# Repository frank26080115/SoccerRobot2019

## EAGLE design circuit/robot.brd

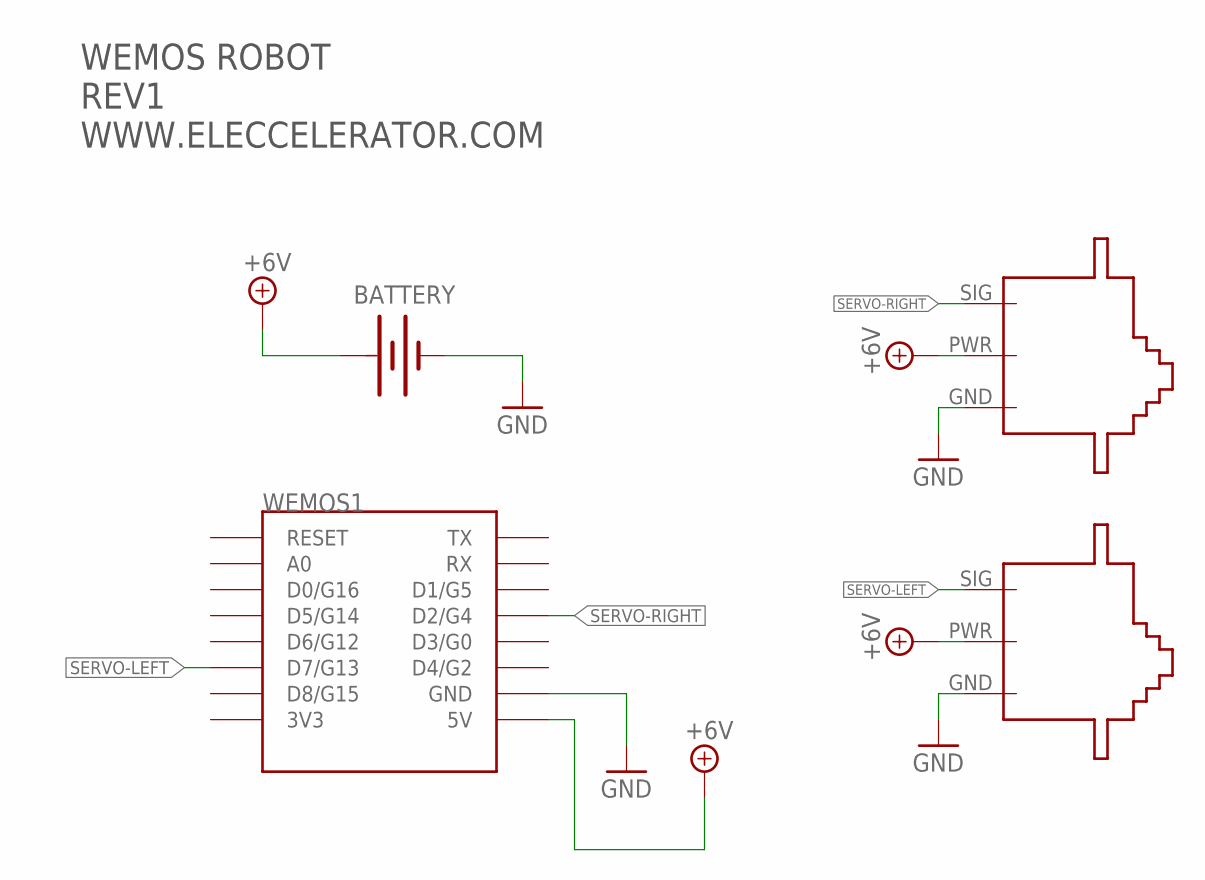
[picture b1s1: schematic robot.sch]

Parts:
BATTERY: BATTERY-WIRE-CONN; BATT-WIRE-CONN
M1: SERVO-FLIPPED
M2: SERVO-1; SERVO
U$1: HACKADAY-14MM; HACKADAY-1
U$9: TEXT-INFO-MINI
WEMOS1: WEMOS-D1-MINI

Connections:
+6V: BATTERY.POS (+), M1.PWR, M2.PWR, WEMOS1.5V
GND: BATTERY.NEG (-), M1.GND, M2.GND, WEMOS1.GND
SERVO-LEFT: M1.SIG, WEMOS1.D7 (D7/G13)
SERVO-RIGHT: M2.SIG, WEMOS1.D2 (D2/G4)

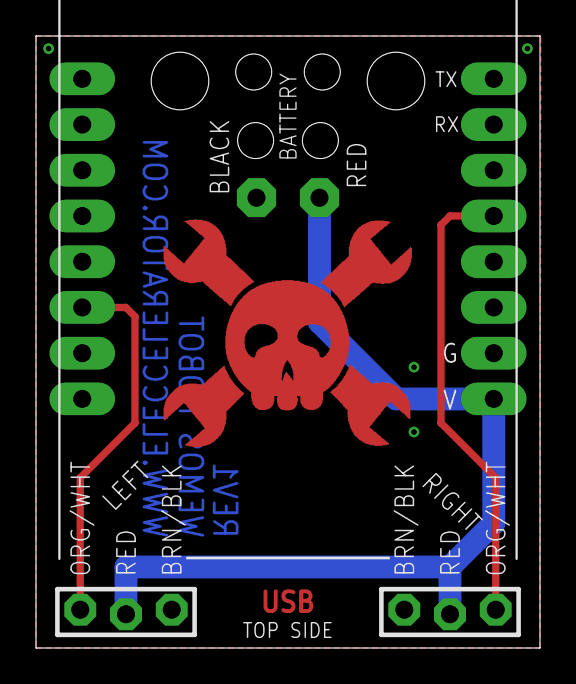
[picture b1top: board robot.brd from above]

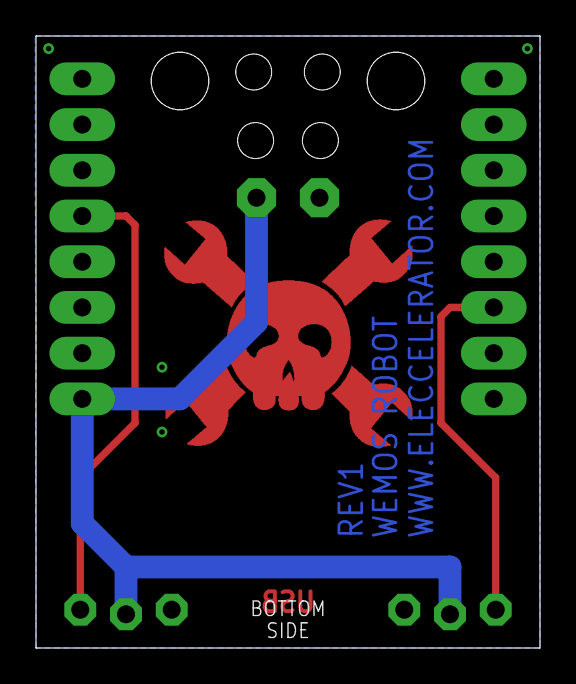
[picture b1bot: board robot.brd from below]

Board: 2 copper layers, 28.0 x 34.0 mm, 6 parts (2 on the bottom side), 4 nets.

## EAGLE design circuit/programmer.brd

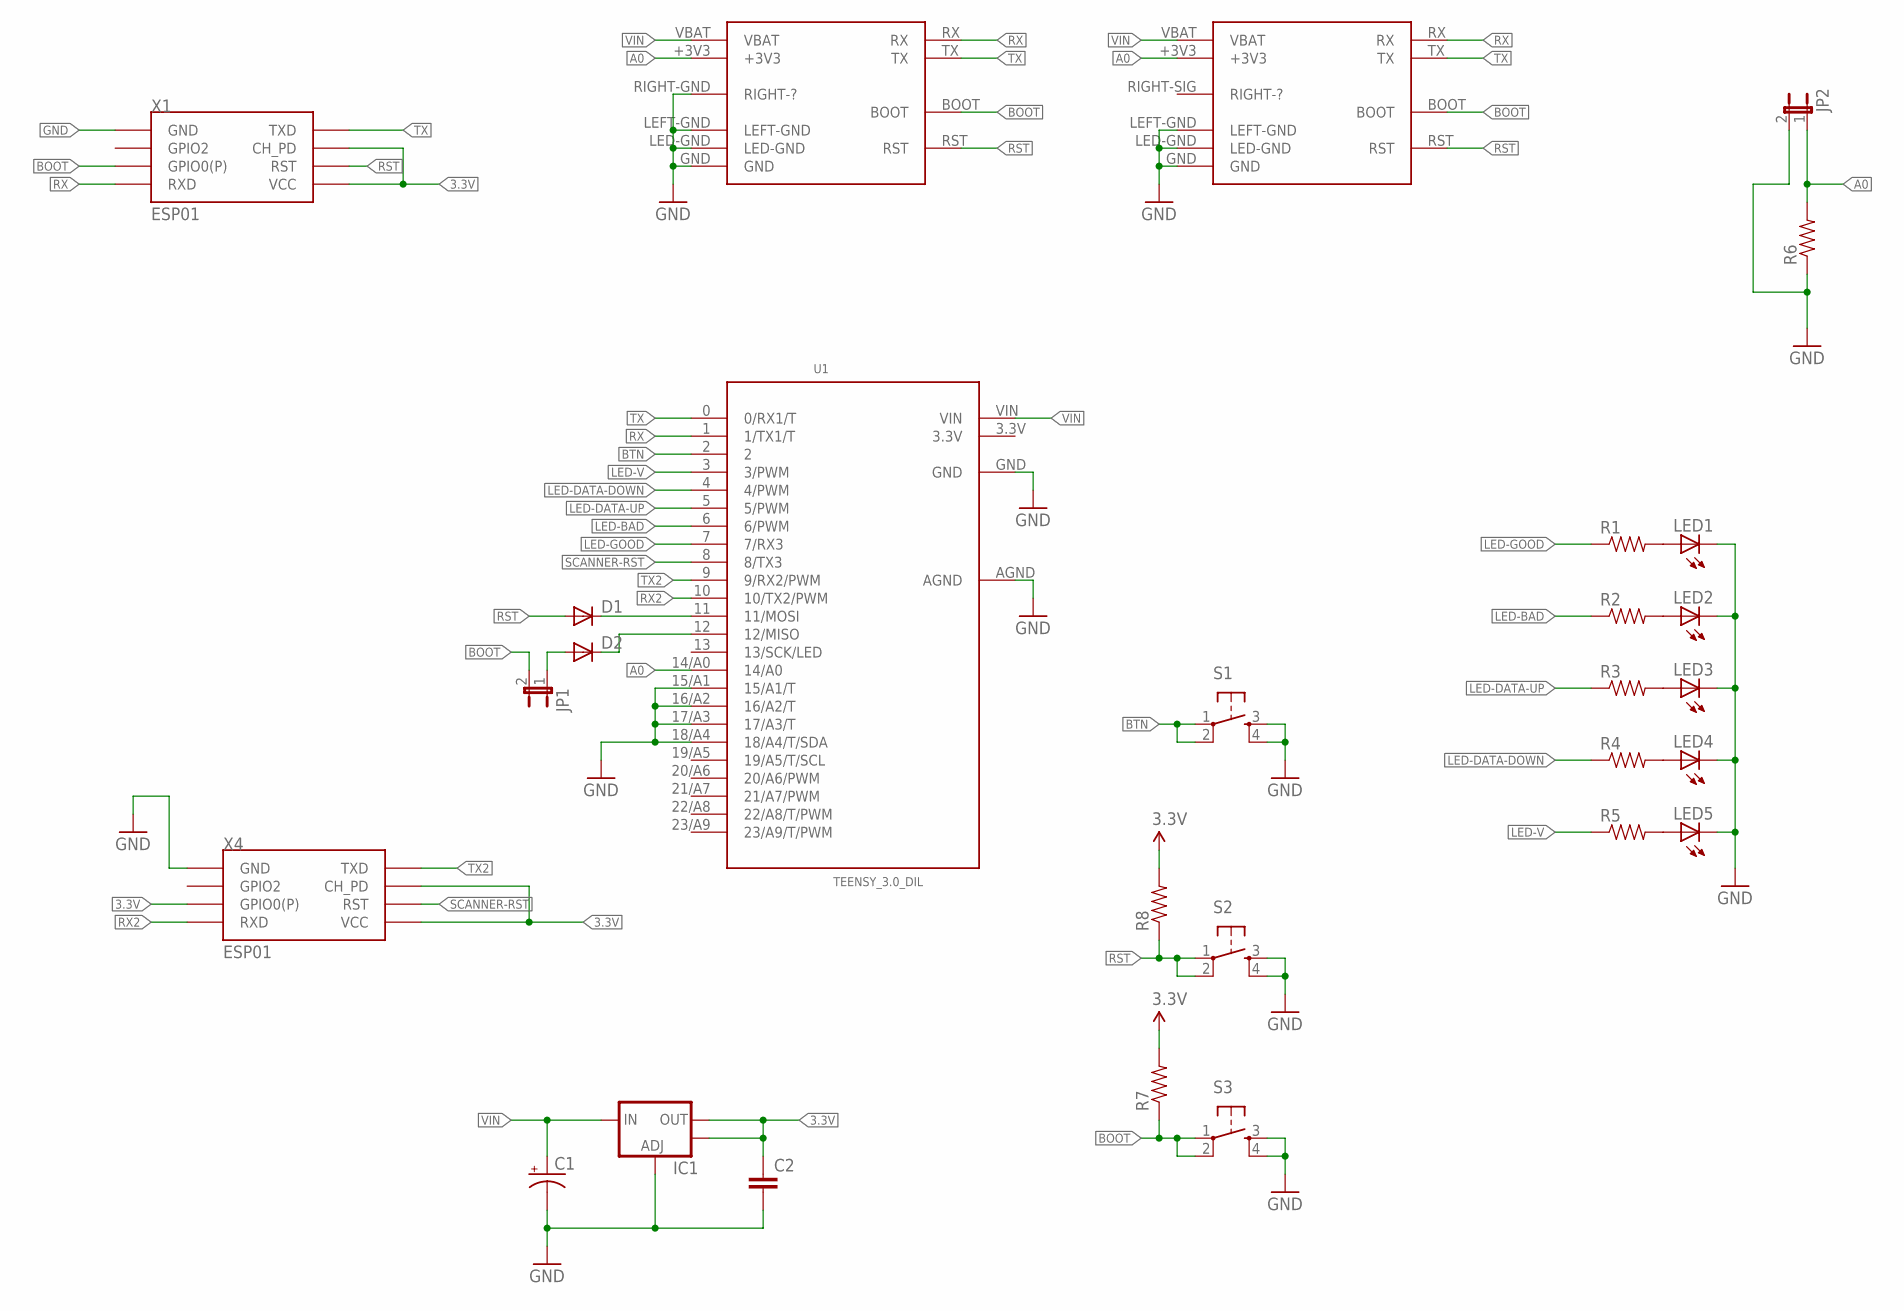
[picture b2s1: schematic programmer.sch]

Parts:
C1: CAP_POLPTH1; CPOL-RADIAL-100UF-25V
C2: CAPPTH2; CAP-PTH-SMALL2
D1, D2: DIODESOD; SOD-323
IC1: V_REG_LM1117SOT223; SOT223
JP1, JP2: JUMPER-2PTH_LOCK; 1X02_LOCK
LED1, LED2, LED3, LED4, LED5: LED5MM
R1, R2, R3, R4, R5, R6, R7, R8: RESISTOR0603-RES; 0603-RES
S1, S2, S3: TAC_SWITCHPTH; TACTILE-PTH
U1: TEENSY_3.0_DIL; TEENSY_3.0-3.2&LC_DIL
X1, X4: ESP01
X2: DIRTCHEAPRX-PROG-MINI; DIRTCHEAPRX_MINI_PROGPINS
X3: DIRTCHEAPRX-PROG-NANO; DIRTCHEAPRX_NANO_PROGPINS

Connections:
3.3V: C2.1, IC1.2 (OUT), IC1.4 (OUT), R7.2, R8.2, U1.3.3V, X1.CH_PD, X1.VCC, X4.CH_PD, X4.GPIO0 (GPIO0(P)), X4.VCC
A0: JP2.1, R6.2, U1.14/A0, X2.+3V3, X3.+3V3
BOOT: JP1.2, R7.1, S3.1, S3.2, X1.GPIO0 (GPIO0(P)), X2.BOOT, X3.BOOT
BTN: S1.1, S1.2, U1.2
GND: C1.2 (-), C2.2, IC1.1 (ADJ), JP2.2, LED1.K (C), LED2.K (C), LED3.K (C), LED4.K (C), LED5.K (C), R6.1, S1.3, S1.4, S2.3, S2.4, S3.3, S3.4, U1.15/A1 (15/A1/T), U1.16/A2 (16/A2/T), U1.17/A3 (17/A3/T), U1.18/A4 (18/A4/T/SDA), U1.AGND, U1.GND, X1.GND, X2.GND, X2.LED-GND, X2.LEFT-GND, X2.RIGHT-GND (RIGHT-?), X3.GND, X3.LED-GND, X3.LEFT-GND, X4.GND
LED-BAD: R2.1, U1.6 (6/PWM)
LED-DATA-DOWN: R4.1, U1.4 (4/PWM)
LED-DATA-UP: R3.1, U1.5 (5/PWM)
LED-GOOD: R1.1, U1.7 (7/RX3)
LED-V: R5.1, U1.3 (3/PWM)
unnamed: D1.1 (C), U1.11 (11/MOSI)
unnamed: LED1.A, R1.2
unnamed: LED2.A, R2.2
unnamed: LED3.A, R3.2
unnamed: LED4.A, R4.2
unnamed: LED5.A, R5.2
unnamed: D2.1 (C), U1.12 (12/MISO)
unnamed: D2.2 (A), JP1.1
RST: D1.2 (A), R8.1, S2.1, S2.2, X1.RST, X2.RST, X3.RST
RX: U1.1 (1/TX1/T), X1.RX (RXD), X2.RX, X3.RX
RX2: U1.10 (10/TX2/PWM), X4.RX (RXD)
SCANNER-RST: U1.8 (8/TX3), X4.RST
TX: U1.0 (0/RX1/T), X1.TX (TXD), X2.TX, X3.TX
TX2: U1.9 (9/RX2/PWM), X4.TX (TXD)
VIN: C1.1 (+), IC1.3 (IN), U1.VIN, X2.VBAT, X3.VBAT

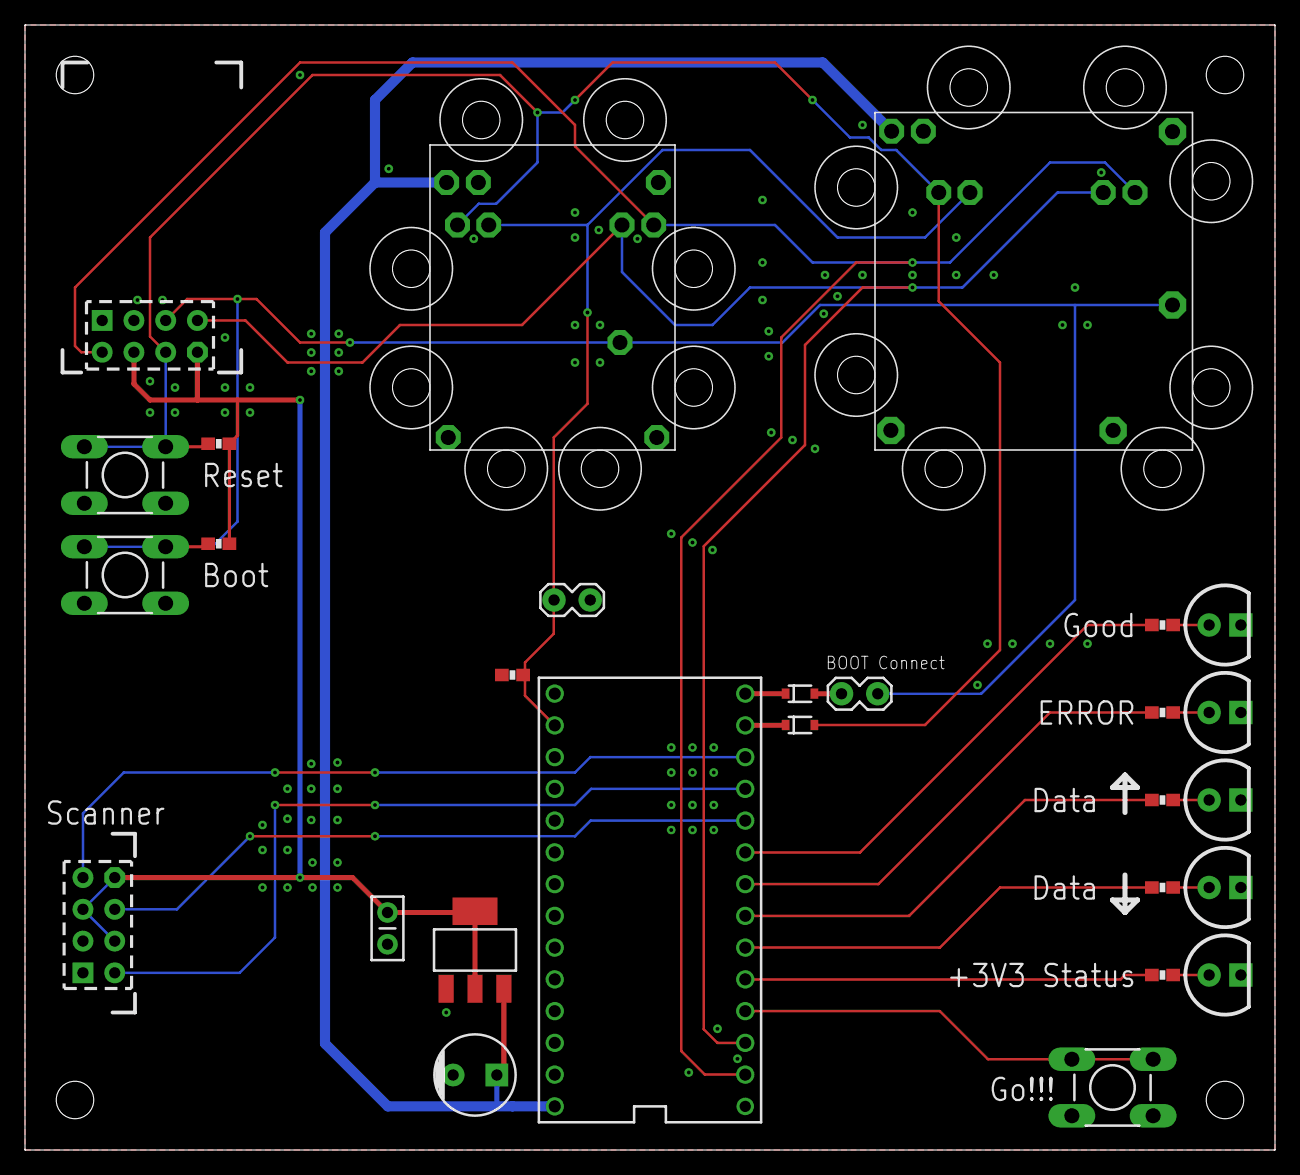
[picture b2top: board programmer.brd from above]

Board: 2 copper layers, 100.0 x 90.0 mm, 28 parts (1 on the bottom side), 25 nets.

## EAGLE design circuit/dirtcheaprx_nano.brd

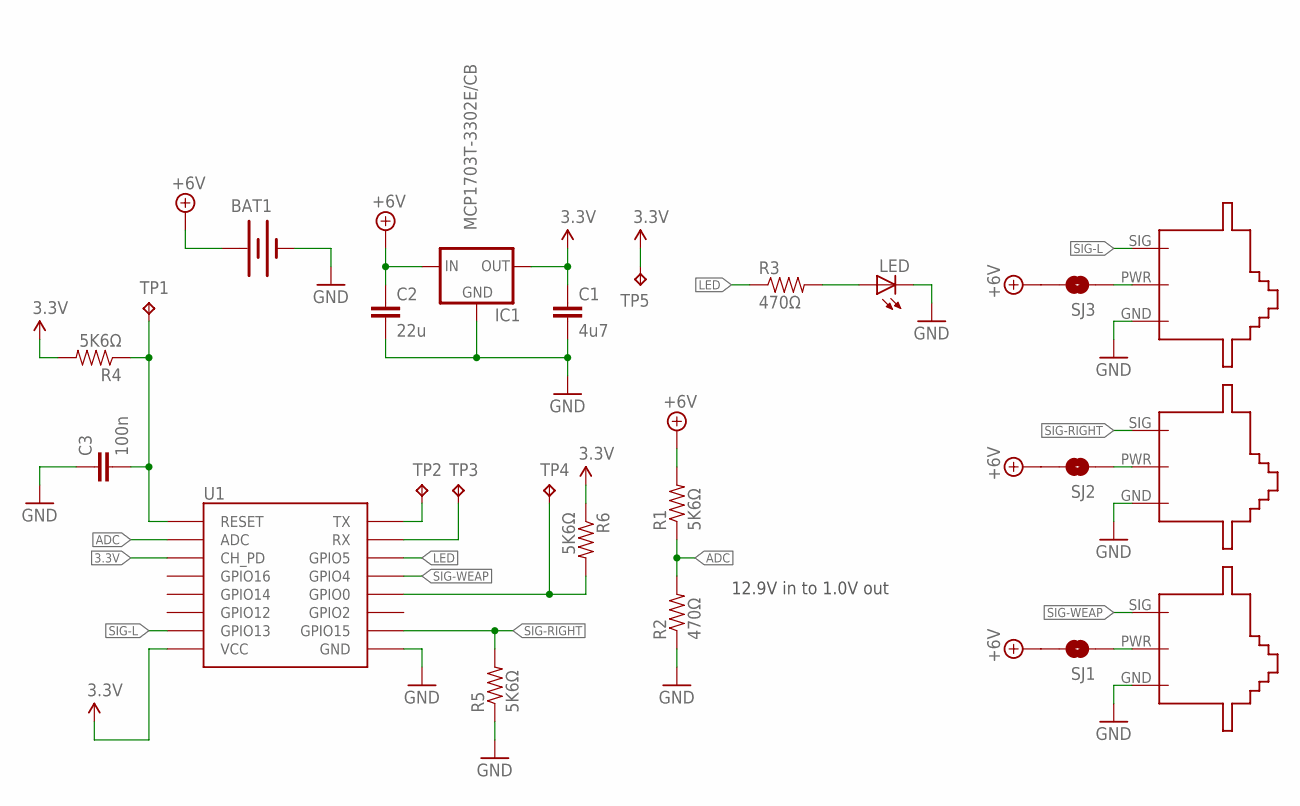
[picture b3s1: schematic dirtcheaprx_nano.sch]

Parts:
BAT1: BATTERY-WIRE-CONN; BATT-WIRE-CONN
C1: 4u7; 0805
C2: 22u; 0805
C3: 100n; 0603-CAP
IC1: MCP1703T-3302E/CB; SOT23-3
LED: LED5MM
R1, R4, R5, R6: 5K6Ω; 0603-RES
R2, R3: 470Ω; 0603-RES
SERVO1: SERVO-SMD-EDGE-1F; SERVO-EDGE-F
SERVO2, SERVO3: SERVO-SMD-EDGE-1; SERVO-EDGE
SJ1, SJ2, SJ3: SOLDERJUMPERNO; SJ_2S-NO
TP1, TP2, TP3, TP4, TP5: TPPAD1-13; P1-13
U1: ESP12SMD; ESP12SE-SMD

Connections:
3.3V: C1.1, IC1.2 (OUT), R4.2, R6.1, TP5.TP, U1.CH_PD, U1.VCC
+6V: BAT1.POS (+), C2.1, IC1.3 (IN), R1.2, SJ1.2, SJ2.2, SJ3.2
ADC: R1.1, R2.2, U1.ADC
GND: BAT1.NEG (-), C1.2, C2.2, C3.1, IC1.1 (GND), LED.K (C), R2.1, R5.1, SERVO1.GND, SERVO2.GND, SERVO3.GND, U1.GND
LED: R3.1, U1.GPIO5
unnamed: LED.A, R3.2
unnamed: SERVO1.PWR, SJ1.1
unnamed: SERVO2.PWR, SJ2.1
unnamed: SERVO3.PWR, SJ3.1
unnamed: C3.2, R4.1, TP1.TP, U1.RESET
unnamed: TP2.TP, U1.TXD0 (TX)
unnamed: TP3.TP, U1.RXD0 (RX)
unnamed: R6.2, TP4.TP, U1.GPIO0
SIG-L: SERVO3.SIG, U1.GPIO13
SIG-RIGHT: R5.2, SERVO2.SIG, U1.GPIO15
SIG-WEAP: SERVO1.SIG, U1.GPIO4

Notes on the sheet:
12.9V in to 1.0V out

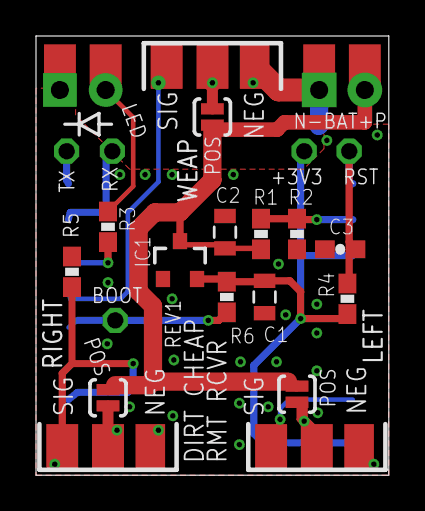
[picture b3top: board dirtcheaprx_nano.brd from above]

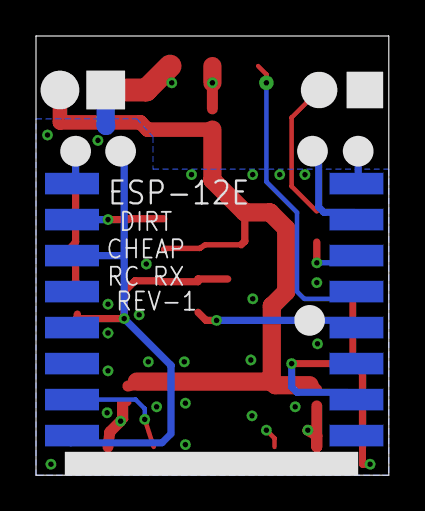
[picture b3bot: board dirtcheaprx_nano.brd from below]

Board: 2 copper layers, 19.6 x 24.4 mm, 24 parts (6 on the bottom side), 16 nets.

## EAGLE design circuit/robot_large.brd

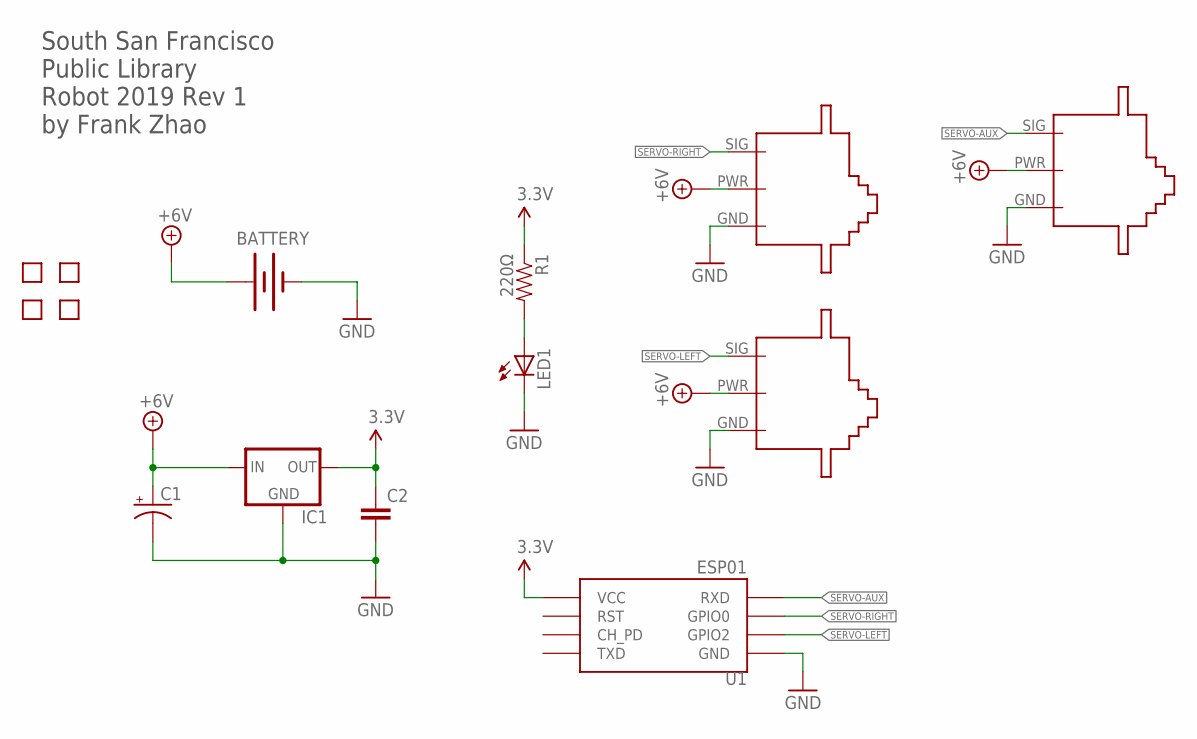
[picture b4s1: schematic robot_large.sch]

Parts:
BATTERY: BATTERY-WIRE-CONN; BATT-WIRE-CONN
C1: CAP_POLPTH1; CPOL-RADIAL-100UF-25V
C2: CAPPTH; CAP-PTH-SMALL
IC1: V_REG_78XXTO-92; TO-92
LED1: LED5MM
M1: SERVO-FLIPPED
M2, M3: SERVO-1; SERVO
R1: 220Ω; AXIAL-0.3-NOVAL
U1: ESP01
U$9: TEXT-INFO
U$10, U$11, U$12, U$13: HOLE; HOLE-2MM

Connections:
3.3V: C2.1, IC1.3 (OUT), R1.P$1 (1), U1.VCC
+6V: BATTERY.POS (+), C1.1 (+), IC1.2 (IN), M1.PWR, M2.PWR, M3.PWR
GND: BATTERY.NEG (-), C1.2 (-), C2.2, IC1.1 (GND), LED1.K (C), M1.GND, M2.GND, M3.GND, U1.GND
unnamed: LED1.A, R1.P$2 (2)
SERVO-AUX: M3.SIG, U1.RX (RXD)
SERVO-LEFT: M1.SIG, U1.GPIO2
SERVO-RIGHT: M2.SIG, U1.GPIO0

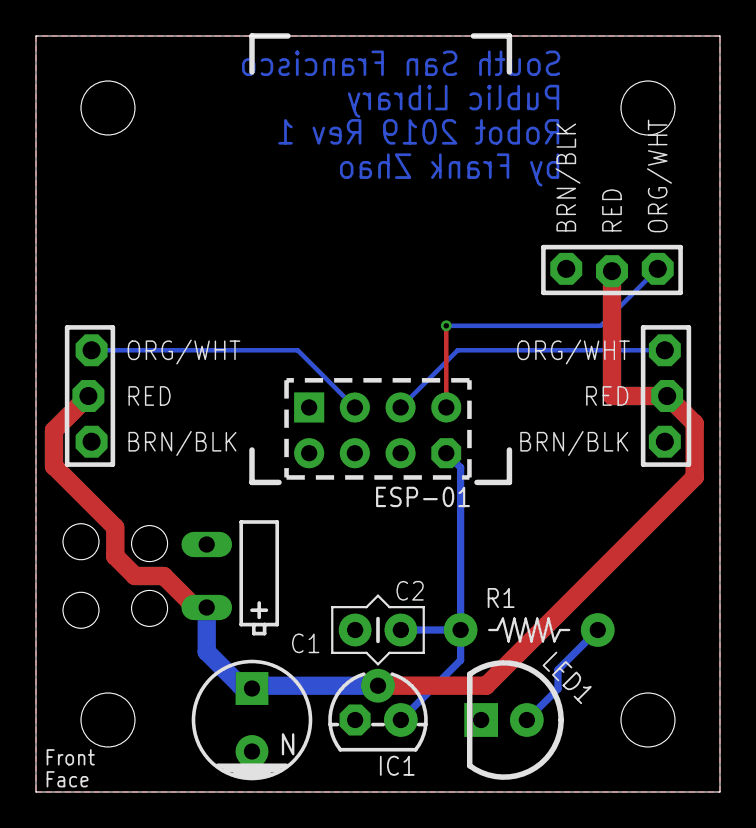
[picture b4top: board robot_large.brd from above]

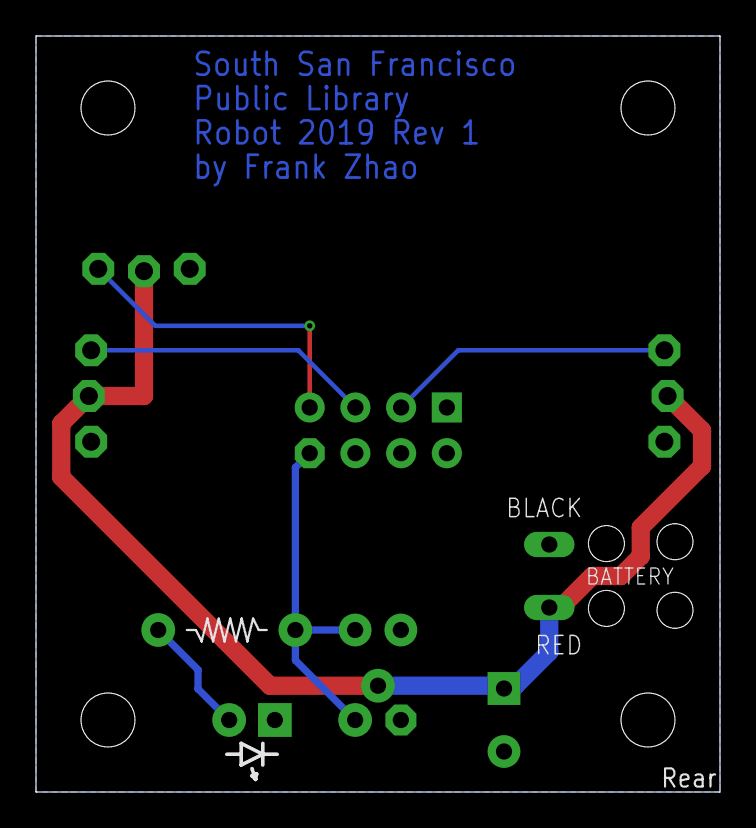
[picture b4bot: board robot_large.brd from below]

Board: 2 copper layers, 38.0 x 42.0 mm, 15 parts (3 on the bottom side), 7 nets.

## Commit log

2018-07-19 dynamic unique SSID and NVM code, compiles
2018-07-19 initial schematic and pcb
2018-07-19 basic robot code, compiles, not tested, no pages
2018-07-20 pcb rev cleanup
2018-07-20 smaller pcb
2018-07-20 more code features
2018-07-20 changed joystick limit area to square instead of circle
2018-07-21 stylistic changes to web ui
2018-07-21 internal debug statements for lib
2018-07-21 few better labels
2018-07-21 actually applies servo flip
2018-07-21 update small PCB with version info
2018-07-22 web stuff works, more settings, PCB configurable
2018-07-23 working servo implementation, tested
2018-07-23 all 3 servos happy, UI tested
2018-07-23 a bit of cleanup and comments
2018-07-23 readServerArg to handle doubles, joystick have a deadzone
2018-07-25 minor display changes, added table border and better debug coords
2018-07-25 added safe mode for debugging
2018-07-25 hexbug beacon untested
2018-07-25 more comm modes for hexbugbeacon
2018-07-25 added packet format comment, added .begin to irsend
2018-07-25 keyboard works great, added a lot of debug
2018-07-25 more debug, tcp seems to work
2018-07-27 working demo
2018-07-27 cmd params set to 8 bit
2018-07-27 hmm reverting soon
2018-07-29 PCBs, first proto batch
2018-07-30 added hardware config header file for new PCB
2018-08-01 nano PCB for dirt cheap rx
2018-08-01 batter monitoring skeleton code
2018-08-02 json reply for battery status, untested
2018-08-02 various methods to factory reset
2018-08-02 minor changes to factory reset conditions
2018-08-02 moved right servo sig trace above danger zone
2018-08-02 fixed XHR status handling in JS
2018-08-03 more browser compatibility?
2018-08-05 more config options, wifi settings, hexblob, untested
2018-08-05 silk over testpoints on pcb
2018-08-07 code organization, also added a way to display HW info
2018-08-08 new config layout, tested hexblob
2018-08-09 trying to fix the NVM read crash
2018-08-09 captive portal example reduced to minimal functionality
2018-08-09 added comment about fixing the NVM loading crashing
2018-08-09 updated ArduinoJson library to latest
2018-08-10 GPIO15 needs to be pulled down, I missed the memo...
2018-08-10 ArduinoJson update broke, put back the github version
2018-08-10 changed NVM struct to a pointer, did not fix loss of AP problem
2018-08-10 battery reading is taking too long? disabling for now, also password is static
2018-08-10 speed up analog reads
2018-08-11 programmer pcb start
2018-08-12 progress on programmer pcb
2018-08-12 fixed analog reading being wrong
2018-08-12 ESP-12 has pins 5 and 4 swapped on silk
2018-08-12 movement debug, less frequent batt reads, better captive portal, check FS
2018-08-12 work on programmer pcb
2018-08-12 fixed movement mathematics
2018-08-12 attempted to add multitouch for buttons, doesn't work
2018-08-12 servo flip drop down bug fix
2018-08-12 startup SPIFFS check fix
2018-08-12 better servo movement reporting
2018-08-13 corrected GPIO4 and GPIO5 mixup in PCBs
2018-08-15 testbench page shows whether touch or mouse
2018-08-15 multitouch buttons working for desktop chrome
2018-08-15 implemented standby button
2018-08-16 connection lost handling on page
2018-08-16 better battery reading
2018-08-17 minor UI fixes
2018-08-17 fixed signal cross reset
2018-08-18 startup diagnostics
2018-08-18 resistor on GPIO0, flipped weap servo connector
2018-08-18 programmer, more vias, disconnectable boot signal
2018-08-18 programmer, changed drill sizes (might need to revert)
2018-08-18 diagnostic for flash size, added eraseConfig to factory reset
2018-08-20 gerbers ordered
2018-08-20 second edition of the diy robot board with LM1117 vreg
2018-08-20 gerber out, added some optional pull-up resistors
2018-08-22 fixed captive portal for android oreo
2018-08-22 always send XHR instead of only when needed
2018-08-24 needed to slow down requests, was causing a crash
2018-08-24 added Wemos based PCB
2018-08-31 variable AJAX refresh rate
